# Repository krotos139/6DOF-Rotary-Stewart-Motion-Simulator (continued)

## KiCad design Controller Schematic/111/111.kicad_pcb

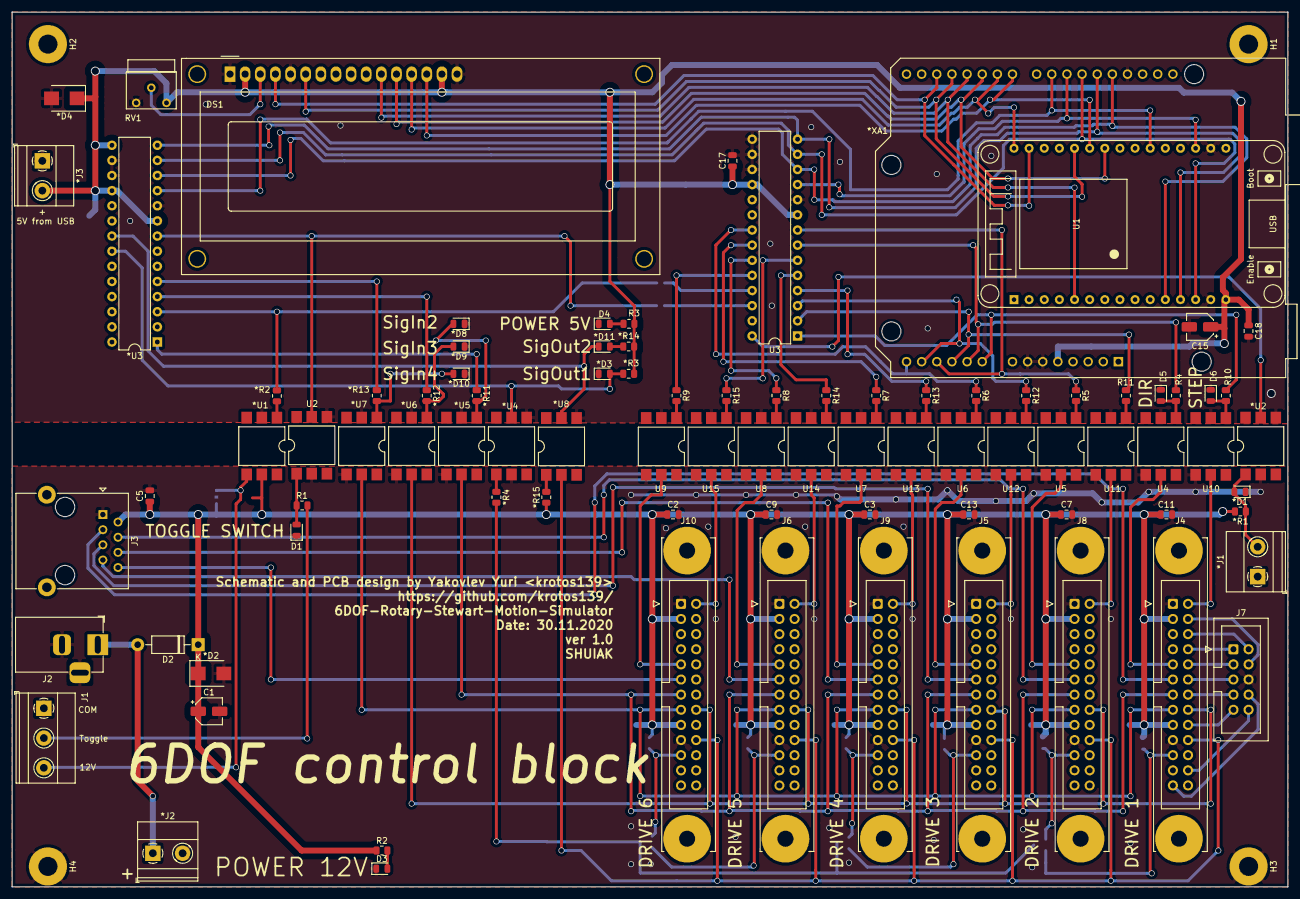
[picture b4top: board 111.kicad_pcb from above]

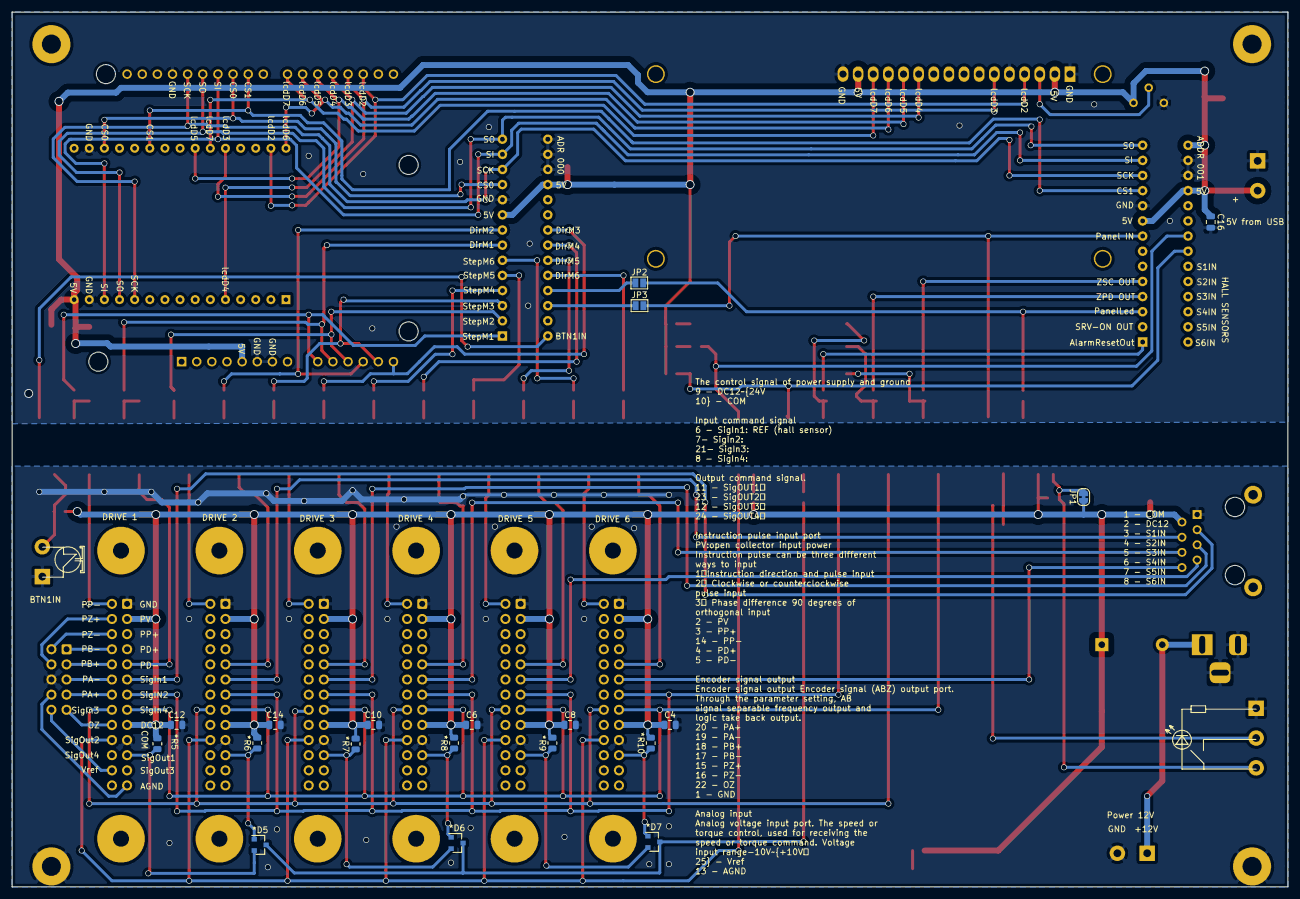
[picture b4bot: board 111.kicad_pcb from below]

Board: 2 copper layers, 214.1 x 146.8 mm, 111 parts (19 on the bottom side), 102 nets.

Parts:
*D1, *D3, *D8, *D9, *D10, *D11: BL-LS0805UYC; LED_0805_2012Metric
*D2, *D4: SM6T22A; D_SMB
*D5, *D6, *D7: BAV23; SOT-23
*J1, *J2, *J3: Screw_Terminal_01x02; TerminalBlock_Phoenix_MKDS-1,5-2_1x02_P5.00mm_Horizontal
*R1, *R3, *R4, *R5, *R6, *R7, *R8, *R9, *R10, *R14, *R15: 330; R_0805_2012Metric
*R2, *R11, *R12, *R13: 100; R_0805_2012Metric
*U1, *U2, *U4, *U5, *U6, *U7, *U8: 4N35; SMDIP-6_W9.53mm
*U3: MCP23SigIn1M17_SP; DIP-28_W7.62mm
*XA1: Arduino_Uno_Shield; Arduino_UNO_R3_WithMountingHoles
C1, C15: 1uF, 50V; CP_Elec_4x5.7
C2, C3, C4, C5, C6, C7, C8, C9, C10, C11, C12, C13, C14, C16, C17, C18: 0.1uF 50V; C_0805_2012Metric
D1, D3, D4, D5, D6: BL-LS0805UYC; LED_0805_2012Metric
D2: 1N4003; D_DO-41_SOD81_P10.16mm_Horizontal
DS1: WC1602A
H1, H2, H3, H4: MountingHole_Pad; MountingHole_3.2mm_M3_Pad
J1: Screw_Terminal_01x03; TerminalBlock_Phoenix_MKDS-1,5-3_1x03_P5.00mm_Horizontal
J2: DS-201; BarrelJack_Horizontal
J3: RJ45; RJ45_Ninigi_GE
J4, J5, J6, J8, J9, J10: Conn_02x13_Top_Bottom; IDC-Header_2x13-1MP_P2.54mm_Latch_Vertical
J7: Conn_02x05_Top_Bottom; IDC-Header_2x05_P2.54mm_Vertical
JP1: SolderJumper_2_Bridged; SolderJumper-2_P1.3mm_Bridged_RoundedPad1.0x1.5mm
JP2, JP3: SolderJumper_2_Open; SolderJumper-2_P1.3mm_Open_Pad1.0x1.5mm
R1, R2, R3: 330; R_0805_2012Metric
R4, R5, R6, R7, R8, R9, R10, R11, R12, R13, R14, R15: 100; R_0805_2012Metric
RV1: R_POT; Potentiometer_Bourns_3339W_Horizontal
U1: ESP32_DevKit_V1_DOIT; esp32_devkit_v1_doit
U2, U4, U5, U6, U7, U8, U9, U10, U11, U12, U13, U14, U15: 4N35; SMDIP-6_W9.53mm
U3: MCP23SigIn1M17_SP; DIP-28_W7.62mm

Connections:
5V: *D4.1, *J3.2, *R3.1, *R14.1, *U3.9, *U3.15, *U3.18, *XA1.5, C15.1, C16.1, C17.1, C18.1, DS1.2, DS1.15, R3.1, RV1.3, U1.15, U3.9, U3.18
#SigIn2: *R11.1, *U3.1
#SigIn3: *R12.1, *U3.3
#SigIn4: *R13.1, *U3.4
/DirM1: *XA1.10, R4.1, U3.7
/DirM2: *XA1.12, R5.1, U3.8
/DirM3: *XA1.14, R6.1, U3.21
/DirM4: R7.1, U3.22
/DirM5: R8.1, U3.23
/DirM6: R9.1, U3.24
/StepM1: *XA1.9, R10.1, U3.1
/StepM2: *XA1.11, R11.1, U3.2
/StepM3: *XA1.13, R12.1, U3.3
/StepM4: R13.1, U3.4
/StepM5: R14.1, U3.5
/StepM6: R15.1, U3.6
BTN1IN: *U2.5, U3.28
COM: *D1.1, *D2.2, *J1.1, *J2.2, *U2.2, *U4.2, *U5.4, *U6.4, *U7.4, C1.2, C2.2, C3.2, C4.2, C5.2, C6.2, C7.2, C8.2, C9.2, C10.2, C11.2, C12.2, C13.2, C14.2, D1.1, D3.1, H3.1, H4.1, J1.1, J2.2, J2.3, J3.1, J4.1, J4.19, J5.1, J5.19, J6.1, J6.19, J7.6, J8.1, J8.19, J9.1, J9.19, J10.1, J10.19, U2.2, U4.4, U5.4, U6.4, U7.4, U8.4, U9.4, U10.4, U11.4, U12.4, U13.4, U14.4, U15.4
CS0: *XA1.25, U1.18, U3.11
CSigIn1M1: *U3.11, *XA1.24, U1.21
DC12: *D2.1, *R1.2, *R5.2, *R6.2, *R7.2, *R8.2, *R9.2, *R10.2, *R15.1, *U1.5, C1.1, C2.1, C3.1, C4.1, C5.1, C6.1, C7.1, C8.1, C9.1, C10.1, C11.1, C12.1, C13.1, C14.1, D2.1, J3.2, J4.3, J4.17, J5.3, J5.17, J6.3, J6.17, J8.3, J8.17, J9.3, J9.17, J10.3, J10.17, JP1.1, R2.1
DM1: J4.9, U4.5
DM2: J8.9, U5.5
DM3: J5.9, U6.5
DM4: J9.9, U7.5
DM5: J6.9, U8.5
DM6: J10.9, U9.5
Earth_Protective: *D3.1, *D4.2, *D8.1, *D9.1, *D10.1, *J3.1, *U1.2, *U2.4, *U3.10, *U3.16, *U3.17, *U4.4, *U5.2, *U6.2, *U7.2, *U8.4, *XA1.6, *XA1.7, *XA1.29, C15.2, C16.2, C17.2, C18.2, D4.1, D5.1, D6.1, DS1.1, DS1.5, DS1.16, RV1.1, U1.14, U1.17, U2.4, U3.10, U3.15, U3.16, U3.17, U4.2, U5.2, U6.2, U7.2, U8.2, U9.2, U10.2, U11.2, U12.2, U13.2, U14.2, U15.2
LCDD2: *XA1.17, DS1.4, U1.29
LCDD3: *XA1.18, DS1.6, U1.26
LCDD4: *XA1.19, DS1.11, U1.5
LCDD5: *XA1.20, DS1.12, U1.24
LCDD6: *XA1.21, DS1.13, U1.30
LCDD7: *XA1.22, DS1.14, U1.25
unnamed: *D1.2, *J1.2, *R1.1, *U2.1
unnamed: *D5.3, *D6.3, *D7.3, *R4.2
unnamed: *D8.2, *R11.2, *U5.1
unnamed: *D9.2, *R12.2, *U6.1
unnamed: *D10.2, *R13.2, *U7.1
unnamed: *D11.2, *R14.2
unnamed: *J2.1, D2.2, J2.1
unnamed: *R2.1, *U1.1
unnamed: *R4.1, *U4.1
unnamed: *R15.2, *U8.1
unnamed: *U1.4, J1.3, JP1.2
unnamed: D1.2, R1.1, U2.1
unnamed: D3.2, R2.2
unnamed: D4.2, R3.2
unnamed: D5.2, R4.2, U4.1
unnamed: D6.2, R10.2, U10.1
unnamed: DS1.3, RV1.2
unnamed: J1.2, R1.2
unnamed: J4.4, J7.4
unnamed: J4.6, J7.2
unnamed: J4.8, J7.1
unnamed: J4.10, J7.3
unnamed: J4.12, J7.5
unnamed: J4.14, J7.7
unnamed: J4.18, J7.9
unnamed: J4.24, J7.10
unnamed: J4.25, J7.8
unnamed: JP2.1, U3.25
unnamed: JP3.1, U3.26
unnamed: R5.2, U5.1
unnamed: R6.2, U6.1
unnamed: R7.2, U7.1
unnamed: R8.2, U8.1
unnamed: R9.2, U9.1
unnamed: R11.2, U11.1
unnamed: R12.2, U12.1
unnamed: R13.2, U13.1
unnamed: R14.2, U14.1
unnamed: R15.2, U15.1
NotSigOut1IN: *D3.2, *R3.2, *U3.22, *U4.5
PanelIN: *U3.8, JP3.2, U2.5
PanelLED: *R2.2, *U3.5, JP2.2
SCK: *U3.12, *XA1.28, U1.11, U3.12
SI: *U3.13, *XA1.26, U1.13, U3.13
SM1: J4.2, U10.5
SM2: J8.2, U11.5
SM3: J5.2, U12.5
SM4: J9.2, U13.5
SM5: J6.2, U14.5
SM6: J10.2, U15.5
SO: *U3.14, *XA1.27, U1.12, U3.14
SigIn1M1: J3.3, J4.11
SigIn1M2: J3.4, J8.11
SigIn1M3: J3.5, J5.11
SigIn1M4: J3.6, J9.11
SigIn1M5: J3.7, J6.11
SigIn1M6: J3.8, J10.11
SigIn2: *U5.5, J4.13, J5.13, J6.13, J8.13, J9.13, J10.13
SigIn3: *U6.5, J4.16, J5.16, J6.16, J8.16, J9.16, J10.16
SigIn4: *U7.5, J4.15, J5.15, J6.15, J8.15, J9.15, J10.15
SigOut1M1: *D5.2, *R5.1, J4.21
SigOut1M2: *D5.1, *R6.1, J8.21
SigOut1M3: *D6.2, *R7.1, J5.21
SigOut1M4: *D6.1, *R8.1, J9.21
SigOut1M5: *D7.2, *R9.1, J6.21
SigOut1M6: *D7.1, *R10.1, J10.21
SigOut2: *U8.2, J4.20, J5.20, J6.20, J8.20, J9.20, J10.20
SigOut2IN: *D11.1, *U3.21, *U8.5

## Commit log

2020-11-08 Added Kompas 3D drawings
2020-11-12 Add correct links for my project to readme
2020-11-17 Controller's software has been updated for our mehanics
2020-11-19 I've added new draws
2020-11-25 I've modified the draws
2020-11-29 I've added new schematic
2020-11-30 PCB updated
2020-12-03 PCB was changed
2020-12-03 I've renamed folders
2020-12-03 project updated
2020-12-04 I've added illustation for technical
2020-12-05 The circuit and board were redesigned after prototyping. Removed all unnecessary. Reduced the PCB.
2020-12-05 Added PCB image
2020-12-07 Drawings was added
2020-12-08 3d model was updated
2020-12-08 drawings was changed
2020-12-10 I've added dwg files for laser cut
2020-12-15 Add schematic for wheel
2021-01-06 I've added schematic for MMOS FFB
2021-01-06 I've modified wheel's schematic and pcb
2021-01-06 I've modified wheel's PCB
2021-01-06 I've added the 'Cases' lib
2021-01-07 TDD Wheel's was changed
2021-01-08 Wheel's PCB changed
2021-01-08 I've modify TDD's PCB.
2021-01-08 TDD's PCB was changed
2021-01-09 I've added pedals board
2021-01-10 I've modified Pedal's PCB. I've added gerber files
2021-01-10 I've added drawing for arm tube
2021-01-16 I've modified schematic and PCB for 6DOF controller
2021-01-18 I've added a connector for connect STM32F407G-DISK1 to the Wheel board
2021-01-18 Wheel's scheme updated
2021-01-18 I've added rear button for logitech h shifter
2021-01-18 I've modified Wheel's scheme and PCB
2021-01-26 I've added supressors for all buttons in the Wheel board
2021-01-26 I've chenged sil layer in the Wheel board
2021-01-28 I've changed wheel's PCB, I've added GERBER files
2021-03-14 I've changed the drawings
